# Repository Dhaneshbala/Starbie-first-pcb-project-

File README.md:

#  Starbie- A tamagotchi and study agent

A small PCB project done with the help of the [SharKingStudios/Starbie](https://github.com) tutorial.

##  What is it?

**Starbie** is a tiny, motion-controlled digital pet. It is basically a desktop Tamagotchi with minimal gameplay buttons.It is also a mini study agent with 
features like Study timer Pomodoro 
 OLED dashboard
 Environment monitor |
Light monitor
 RGB status LED 
 Buzzer alerts
 Tilt controls
 Session tracking 

## Project Details
- **Custom Hardware:** A compact custom PCB designed for the Starbie digital pet.
- **Microcontroller:** Seeed Studio XIAO ESP32-C3.
- **Display:** A small display used to show Starbie's face, menus, and pet information.
- **Motion Control:** The board uses movement and tilting to interact with Starbie.
- **Sensors:** Sensors are used to detect movement and environmental information.
- **Interaction:** Starbie responds to tilting and shaking, with a tilt-controlled radial menu and different pet behaviours.
- **Firmware:** Arduino firmware runs on the XIAO ESP32-C3 and controls the display, sensors, and interactions.
- **PCB Design:** The project includes the KiCad schematic and PCB layout files.
- **Manufacturing:** The original project includes PCB fabrication files and a bill of materials.

### Hardware
- **Microcontroller:** Seeed Studio XIAO ESP32-C3
* **Display:** SSD1306 0.96" I2C OLED *
* **Motion/Tilt:** MPU6050 / GY-521 6-Axis IMU*
* **Climate:** DHT11 Temperature & Humidity Sensor
* **Light:** LDR (Light Dependent Resistor) + 10k pull-down resistor
* **Status Indicator:** RGB LED (Common Cathode) + inline resistors (220/ 100 / 100)
* **Audio Alerts:** Passive Buzzer driven by an NPN transistor & flyback protection diode
* **Buttons:** 2 Tactile Buttons
* **Note on 3D Renders:** The SSD1306 OLED and MPU6050 IMU are external plug-in sub-modules. They will not be visible on standard 3D PCB fabrication renders.

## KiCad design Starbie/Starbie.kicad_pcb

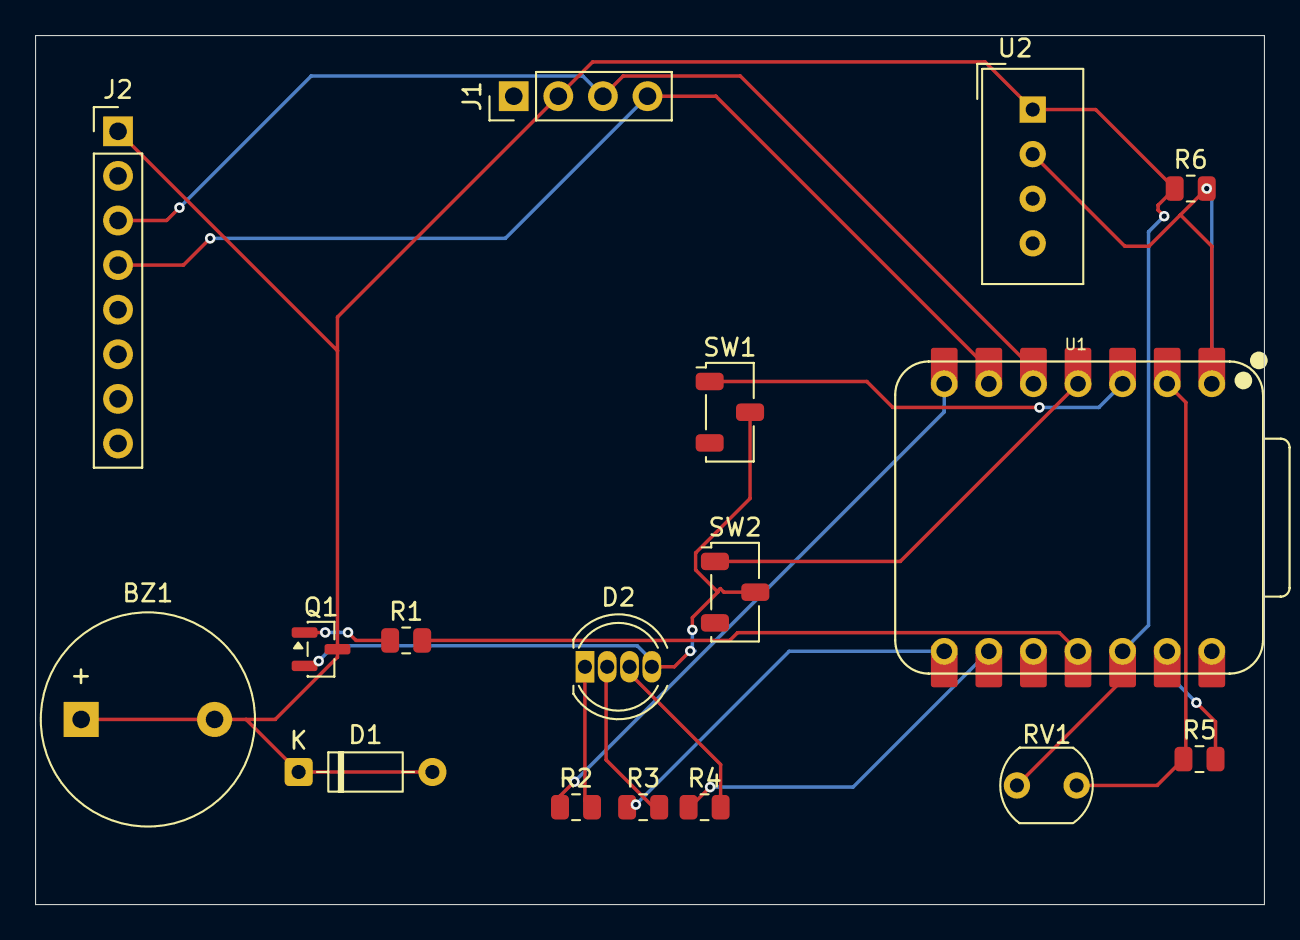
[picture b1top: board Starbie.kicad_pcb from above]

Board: 2 copper layers, 70.0 x 49.5 mm, 17 parts (0 on the bottom side), 16 nets.

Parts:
BZ1: Buzzer; Buzzer_12x9.5RM7.6
D1: 1N4148; D_DO-35_SOD27_P7.62mm_Horizontal
D2: LED_RGBK; LED_D5.0mm-4_RGB
J1: Conn_01x04_Pin; PinHeader_1x04_P2.54mm_Vertical
J2: Conn_01x08_Pin; PinHeader_1x08_P2.54mm_Vertical
Q1: Q_NPN_BEC; SOT-23
R1: 1K; R_0805_2012Metric
R2: 220; R_0805_2012Metric
R3, R4: 100; R_0805_2012Metric
R5, R6: 10K; R_0805_2012Metric
RV1: LDR; R_LDR_5.1x4.3mm_P3.4mm_Vertical
SW1, SW2: SW_Push; Nidec_Copal_CAS-120A
U1: XIAO-ESP32-C3-SMD; XIAO-ESP32-C6-DIP
U2: DHT11; Aosong_DHT11_5.5x12.0_P2.54mm

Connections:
+3.3V: BZ1.1 (+), BZ1.2 (-), D1.1 (K), D1.2 (A), J1.2, J2.1, Q1.3 (C), R6.1, RV1.1, U1.12 (3V3_OUT), U2.1 (VDD)
/Btn1: SW1.1, U1.3 (D2)
/Btn2: SW2.1, U1.4 (D3)
/Buz_Sig: R1.2, U1.11 (D10)
/DHT11 DATA: R6.2, U1.1 (D0), U2.2 (DATA)
/LDR_SIG: R5.1, RV1.2, U1.2 (D1)
/Led_B: R4.1, U1.9 (D8)
/Led_G: R3.1, U1.8 (D7)
/Led_R: R2.1, U1.7 (D6)
/SCL: J1.3, J2.3, U1.5 (D4)
/SDA: J1.4, J2.4, U1.6 (D5)
GND: D2.4 (K), J1.1, J2.2, Q1.2 (E), R5.2, SW1.2, SW2.2, U1.13 (GND), U2.4 (GND)
unnamed: D2.3 (BA), R4.2
unnamed: D2.2 (GA), R3.2
unnamed: D2.1 (RA), R2.2
unnamed: Q1.1 (B), R1.1
